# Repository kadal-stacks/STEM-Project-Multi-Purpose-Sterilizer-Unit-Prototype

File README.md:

# STEM Project: Multi-Purpose Sterilizer Unit Prototype

> A student engineering research project exploring a modular, multi-purpose treatment chamber with an embedded controller. The design and its performance are still under study.

## Visual references

The photographs below are **real reference images found on Wikimedia Commons**, not images of our prototype. They provide context for existing UV treatment equipment and possible emitter types. Product specifications in a photo must not be taken as the specification for our own design.

<table>
  <tr>
    <td align="center" width="50%">
      
      <br /><sub><b>Enclosed UV cabinet</b><br />PT SUM HING INDONESIA · <a href="https://creativecommons.org/licenses/by-sa/4.0/">CC BY-SA 4.0</a></sub>
    </td>
    <td align="center" width="50%">
      
      <br /><sub><b>UV treatment in a cabinet</b><br />Orla Keogh · <a href="https://creativecommons.org/licenses/by/4.0/">CC BY 4.0</a></sub>
    </td>
  </tr>
  <tr>
    <td align="center" width="50%">
      
      <br /><sub><b>Germicidal fluorescent lamp</b><br />Atlant · <a href="https://creativecommons.org/licenses/by/2.5/">CC BY 2.5</a></sub>
    </td>
    <td align="center" width="50%">
      
      <br /><sub><b>UV-C LED module</b><br />Morrow363 · <a href="https://creativecommons.org/licenses/by-sa/4.0/">CC BY-SA 4.0</a></sub>
    </td>
  </tr>
</table>

<sub>Image attribution and licensing details are listed in the [component price study](docs/studi-harga-komponen.md). Images are linked from their original Wikimedia Commons files and are not endorsements or proposed final components.</sub>

## Documentation

- **[Component Price Study / BOM Review](docs/studi-harga-komponen.md)**: marketplace price observations, component comparison, preliminary budget, and purchase checks.
- **[Optimized schematic v1.6](docs/schematic-optimized-v1.svg)** and [design notes](docs/schematic-optimized-v1.md): monochrome circuit-style schematic mapped to STC8G1K08A-36I-DFN8 pins, LCD I²C, door monitoring, Start/Stop, relay/MOSFET driver, and separate mains-interlock boundary.
- [Component-level schematic visual](docs/schematic-komponen-visual-v0.svg) and [earlier low-voltage draft](docs/schematic-low-voltage-v0.svg) are retained as historical references.

> **Hardware note:** the selected STC8G1K08A-36I is a DFN8 0.5 mm-pitch part. It cannot be soldered straight into a standard matrix board; a compatible 0.5 mm DFN8 breakout or custom PCB/SMT assembly is required. The Indonesian BOM subtotal currently excludes this adapter/assembly cost.
>
> **Image policy:** photographs are external reference imagery from Wikimedia Commons. They are not images of this prototype and are not endorsements of the project. Attribution and license links are documented in the BOM review.

## Candidate hardware marks

<p align="center">
  
  <br /><sub>The RISC-V mark identifies the architecture of the CH32V003 candidate only. It does not indicate final MCU selection or endorsement by RISC-V.</sub>
</p>

## Current status

**Phase:** feasibility study and component price review. No final bill of materials (BOM), schematic, firmware architecture, validated treatment process, or electrical safety certification has been completed.

### Current design considerations

- Modular removable rack concept for different item sizes.
- Candidate MCU platforms: STC8H1K08 and CH32V003. Selection is not final.
- 16x2 display and door-state input are considered for the user interface.
- UV-C hardware, ballast/driver, enclosure, interlock, and independent cutoff need careful specification before any powered test.

## Safety and scope

**UV-C radiation and mains voltage can cause serious injury.** Do not operate an exposed UV-C source. Any future prototype must be reviewed for an opaque enclosure, fail-safe door interlock, independent safety cutoff, and appropriate electrical protection. Do not claim sterilization without suitable process and microbiological validation.

This repository is for educational and study-assignment purposes. The prototype is preliminary and is not intended for commercial use.

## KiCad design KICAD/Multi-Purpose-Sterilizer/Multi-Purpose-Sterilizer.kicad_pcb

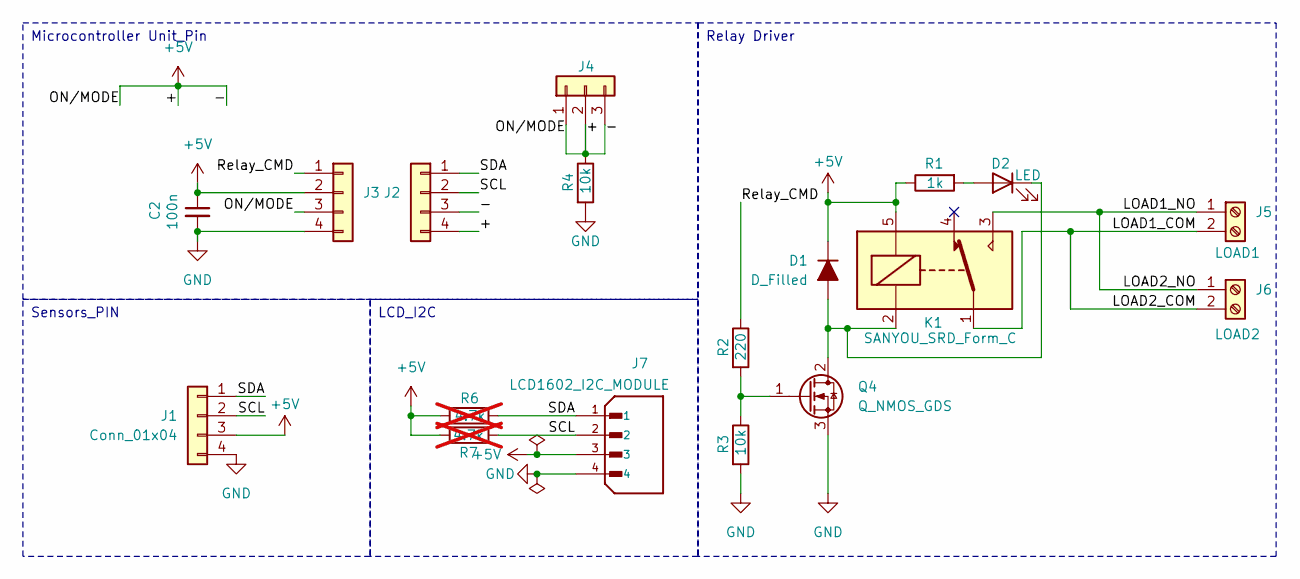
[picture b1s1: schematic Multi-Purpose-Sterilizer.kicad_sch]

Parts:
C2: 100n; C_Disc_D5.0mm_W2.5mm_P5.00mm
D1: D_Filled; D_DO-41_SOD81_P10.16mm_Horizontal
D2: LED; LED_D3.0mm_FlatTop
J1: Conn_01x04; JST_EH_B4B-EH-A_1x04_P2.50mm_Vertical
J2, J3: Conn_01x04; PinSocket_1x04_P2.54mm_Vertical
J4: Conn_01x03; JST_EH_B3B-EH-A_1x03_P2.50mm_Vertical
J5: LOAD1; TerminalBlock_Phoenix_MKDS-1-2-3.81_1x02_P3.81mm_Horizontal
J6: LOAD2; TerminalBlock_Phoenix_MKDS-1-2-3.81_1x02_P3.81mm_Horizontal
J7: LCD1602_I2C_MODULE; JST_XH_B4B-XH-A_1x04_P2.50mm_Vertical; PARTREV 7/4/21
K1: SANYOU_SRD_Form_C; Relay_SPDT_SANYOU_SRD_Series_Form_C
Q4: Q_NMOS_GDS; TO-220-3_Vertical
R1: 1k; R_Axial_DIN0207_L6.3mm_D2.5mm_P10.16mm_Horizontal
R2: 220; R_Axial_DIN0207_L6.3mm_D2.5mm_P10.16mm_Horizontal
R3, R4: 10k; R_Axial_DIN0207_L6.3mm_D2.5mm_P10.16mm_Horizontal
R6, R7: 4.7k; R_Axial_DIN0207_L6.3mm_D2.5mm_P10.16mm_Horizontal; not fitted

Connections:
+5V: C2.1, D1.1 (K), J1.3, J2.3, J2.4, J3.2, J3.3, J4.1, J4.2, J4.3, J7.3, K1.5, R1.1, R4.1, R6.2, R7.1
/LOAD1_COM: J5.2, J6.2, K1.1
/LOAD1_NO: J5.1, J6.1, K1.3
/Relay_CMD: J3.1, R2.1
/SCL: J1.2, J2.2, J7.2, R7.2
/SDA: J1.1, J2.1, J7.1, R6.1
GND: C2.2, J1.4, J3.4, J7.4, Q4.3 (S), R3.2, R4.2
unnamed: D1.2 (A), D2.1 (K), K1.2, Q4.2 (D)
unnamed: D2.2 (A), R1.2
unnamed: Q4.1 (G), R2.2, R3.1

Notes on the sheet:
Microcontroller Unit_Pin
Relay Driver
Sensors_PIN
LCD_I2C

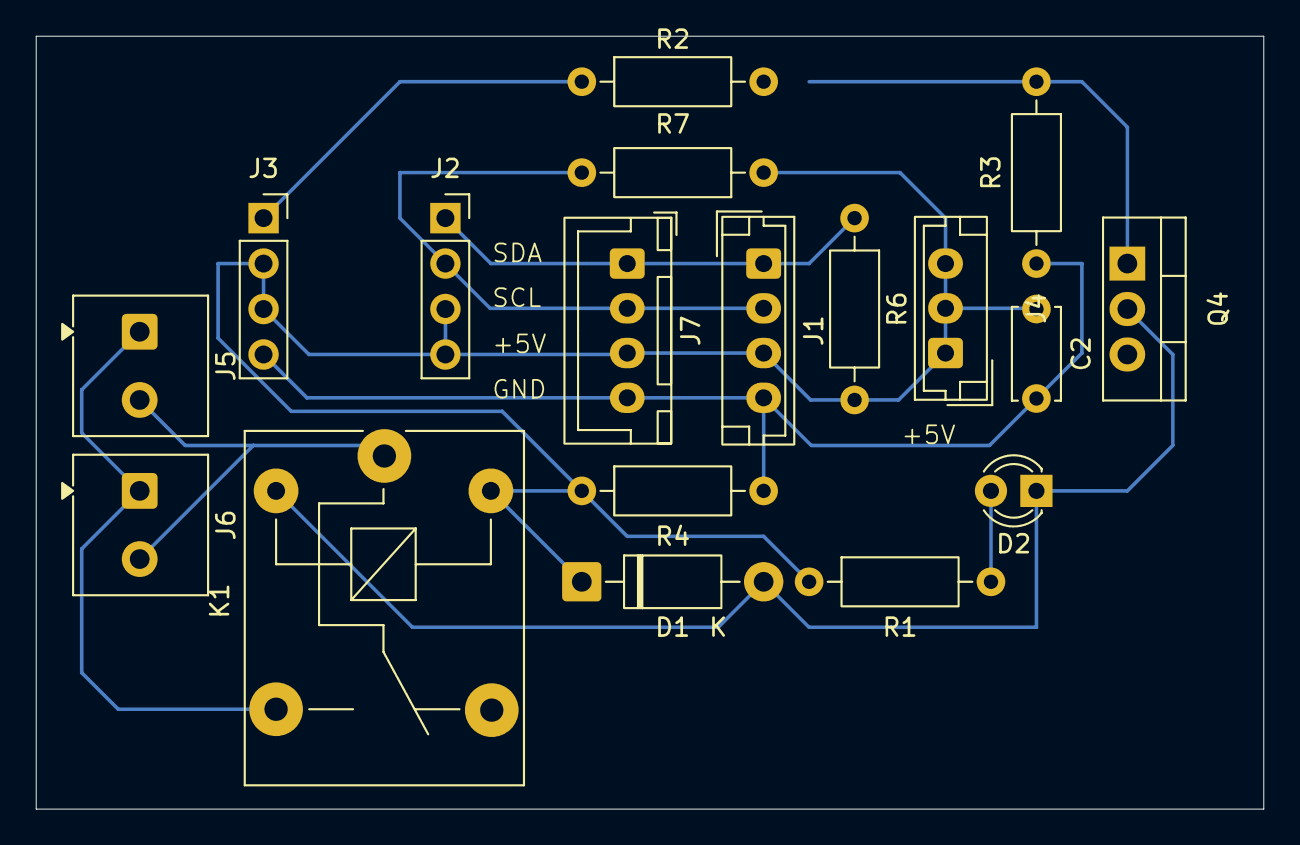
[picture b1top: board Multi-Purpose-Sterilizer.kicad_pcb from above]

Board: 2 copper layers, 68.6 x 43.2 mm, 18 parts (0 on the bottom side), 10 nets.

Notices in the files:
README.md:
Project source license: The Unlicense
